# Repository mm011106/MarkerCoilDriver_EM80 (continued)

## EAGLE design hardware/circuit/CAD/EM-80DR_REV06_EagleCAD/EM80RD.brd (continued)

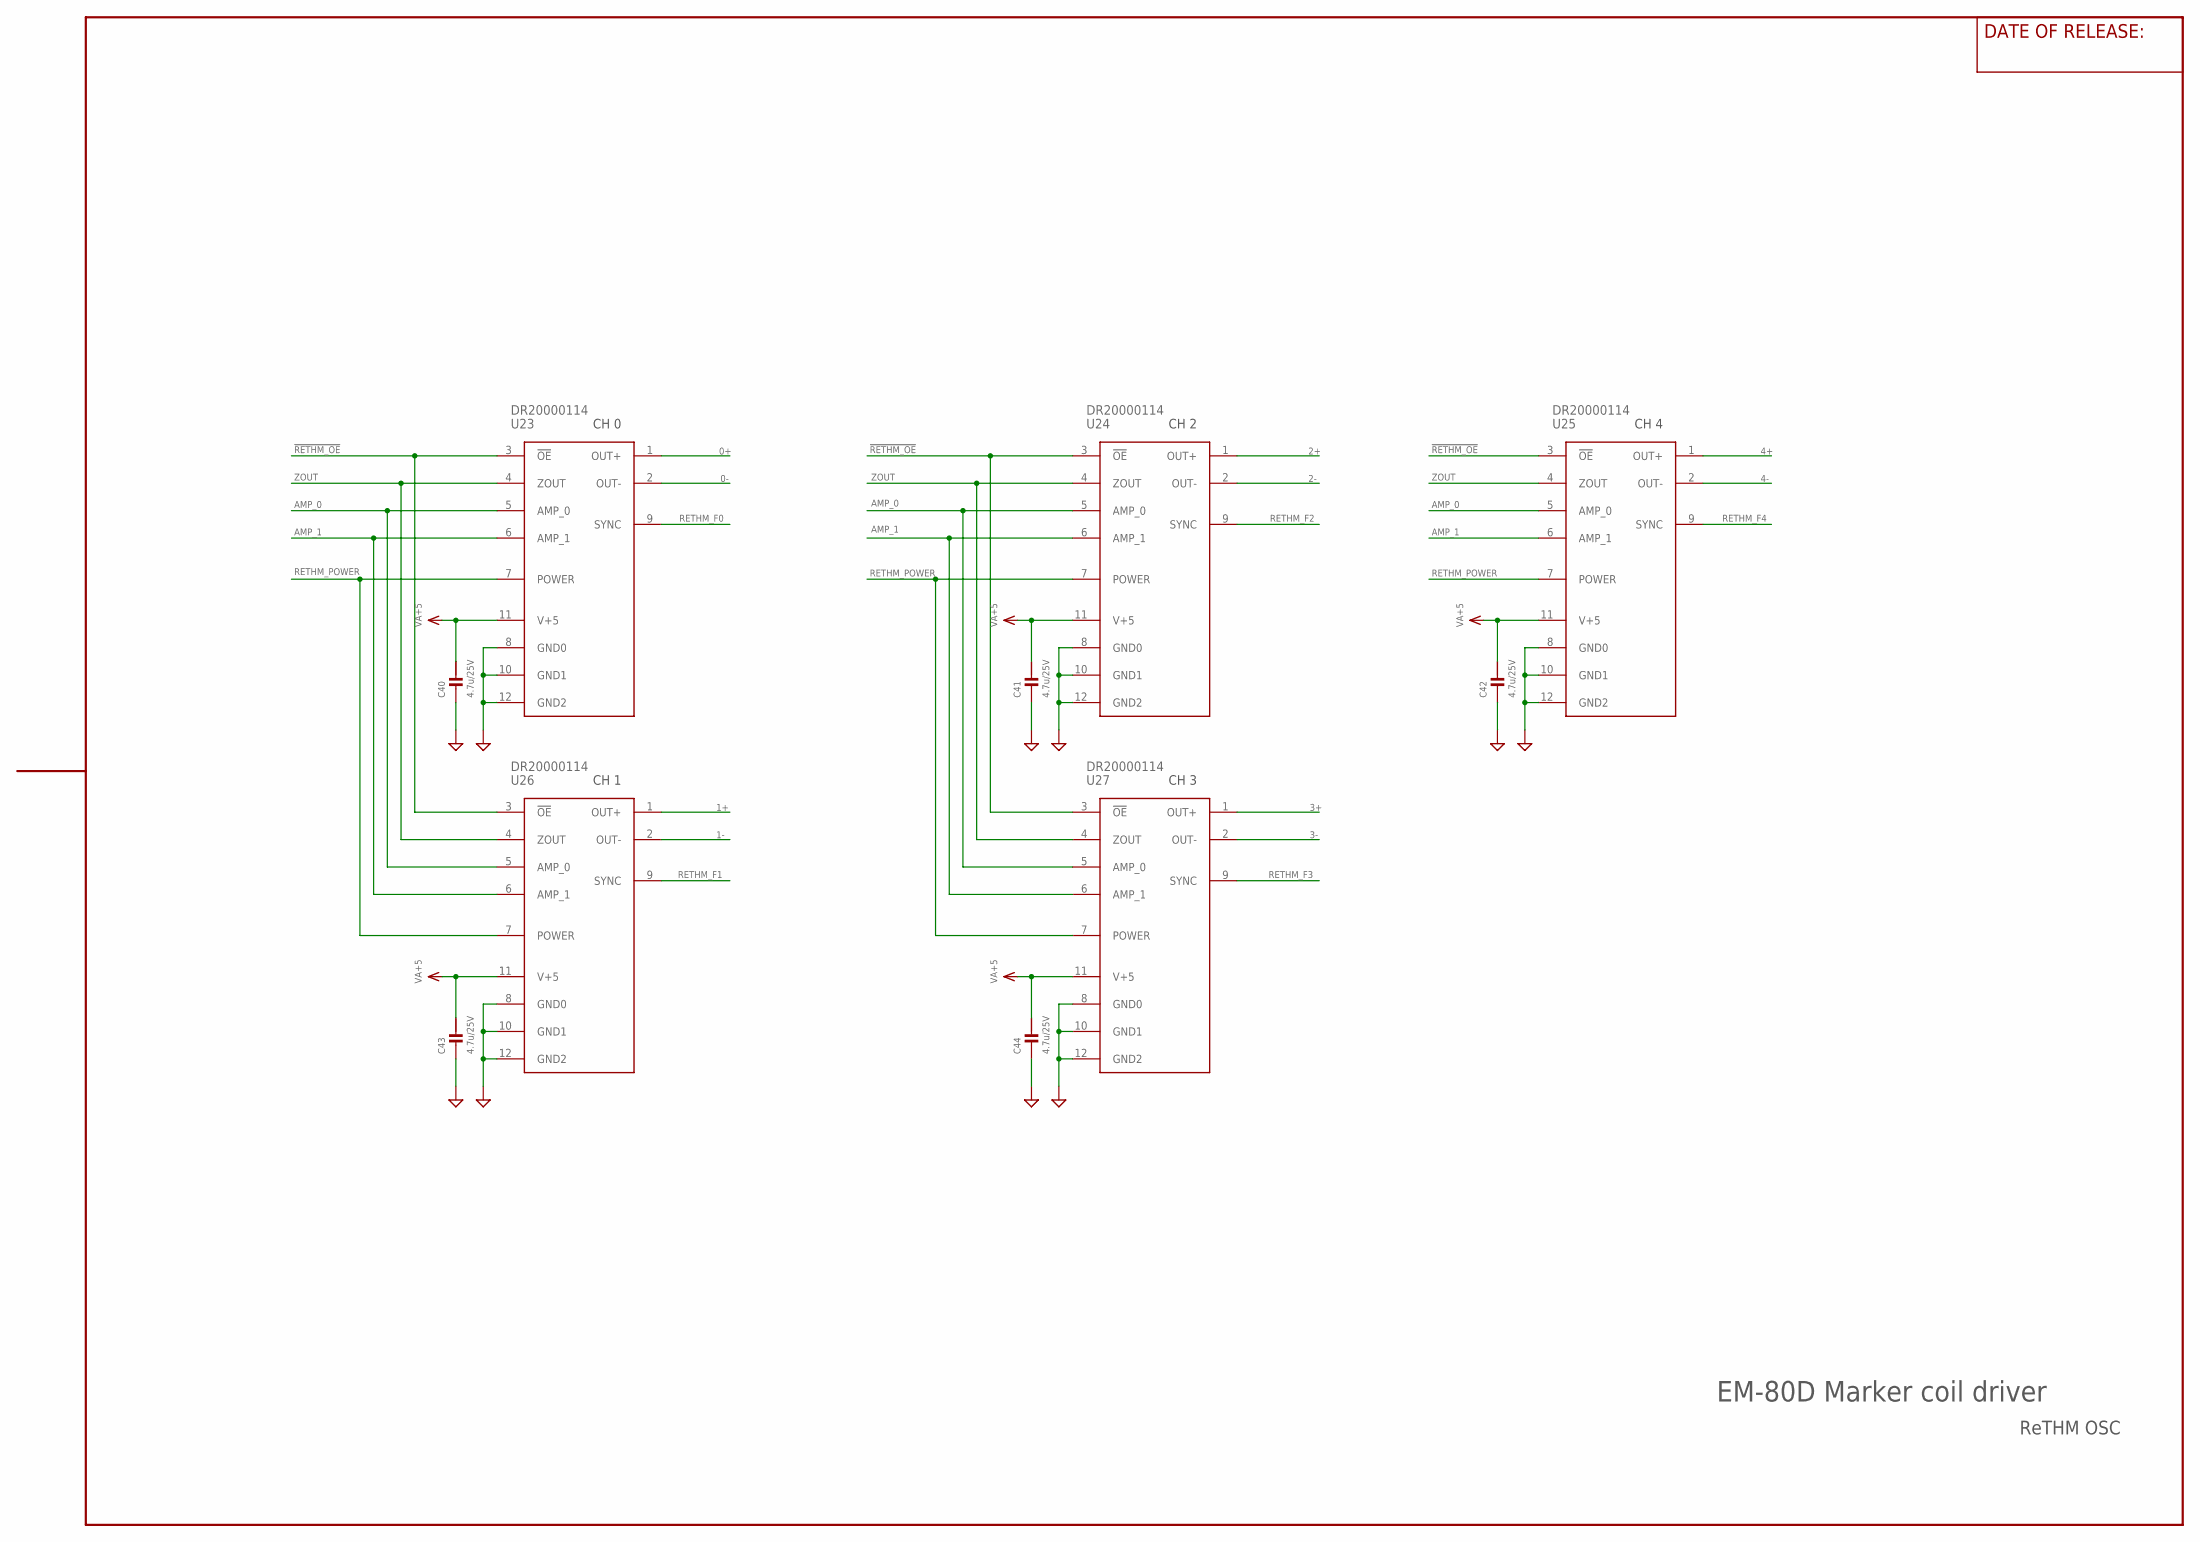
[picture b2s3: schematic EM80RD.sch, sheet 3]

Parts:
C40, C41, C42, C43, C44: 4.7u/25V; CM2012
U23, U24, U25, U26, U27: DR20000114

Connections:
0+: U23.1 (OUT+); also elsewhere on the board
0-: U23.2 (OUT-); also elsewhere on the board
1+: U26.1 (OUT+); also elsewhere on the board
1-: U26.2 (OUT-); also elsewhere on the board
2+: U24.1 (OUT+); also elsewhere on the board
2-: U24.2 (OUT-); also elsewhere on the board
3+: U27.1 (OUT+); also elsewhere on the board
3-: U27.2 (OUT-); also elsewhere on the board
4+: U25.1 (OUT+); also elsewhere on the board
4-: U25.2 (OUT-); also elsewhere on the board
!RETHM_OE: U23.3 (!OE), U24.3 (!OE), U25.3 (!OE), U26.3 (!OE), U27.3 (!OE); also elsewhere on the board
AGND: C40.2, C41.2, C42.2, C43.2, C44.2, U23.8 (GND0), U23.10 (GND1), U23.12 (GND2), U24.8 (GND0), U24.10 (GND1), U24.12 (GND2), U25.8 (GND0), U25.10 (GND1), U25.12 (GND2), U26.8 (GND0), U26.10 (GND1), U26.12 (GND2), U27.8 (GND0), U27.10 (GND1), U27.12 (GND2); also elsewhere on the board
AMP_0: U23.5 (AMP_0), U24.5 (AMP_0), U25.5 (AMP_0), U26.5 (AMP_0), U27.5 (AMP_0); also elsewhere on the board
AMP_1: U23.6 (AMP_1), U24.6 (AMP_1), U25.6 (AMP_1), U26.6 (AMP_1), U27.6 (AMP_1); also elsewhere on the board
RETHM_F0: U23.9 (SYNC); also elsewhere on the board
RETHM_F1: U26.9 (SYNC); also elsewhere on the board
RETHM_F2: U24.9 (SYNC); also elsewhere on the board
RETHM_F3: U27.9 (SYNC); also elsewhere on the board
RETHM_F4: U25.9 (SYNC); also elsewhere on the board
RETHM_POWER: U23.7 (POWER), U24.7 (POWER), U25.7 (POWER), U26.7 (POWER), U27.7 (POWER); also elsewhere on the board
VA+5: C40.1, C41.1, C42.1, C43.1, C44.1, U23.11 (V+5), U24.11 (V+5), U25.11 (V+5), U26.11 (V+5), U27.11 (V+5); also elsewhere on the board
ZOUT: U23.4 (ZOUT), U24.4 (ZOUT), U25.4 (ZOUT), U26.4 (ZOUT), U27.4 (ZOUT); also elsewhere on the board

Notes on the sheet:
ReTHM OSC
CH 0
CH 1
CH 2
CH 3
CH 4
EM-80D Marker coil driver

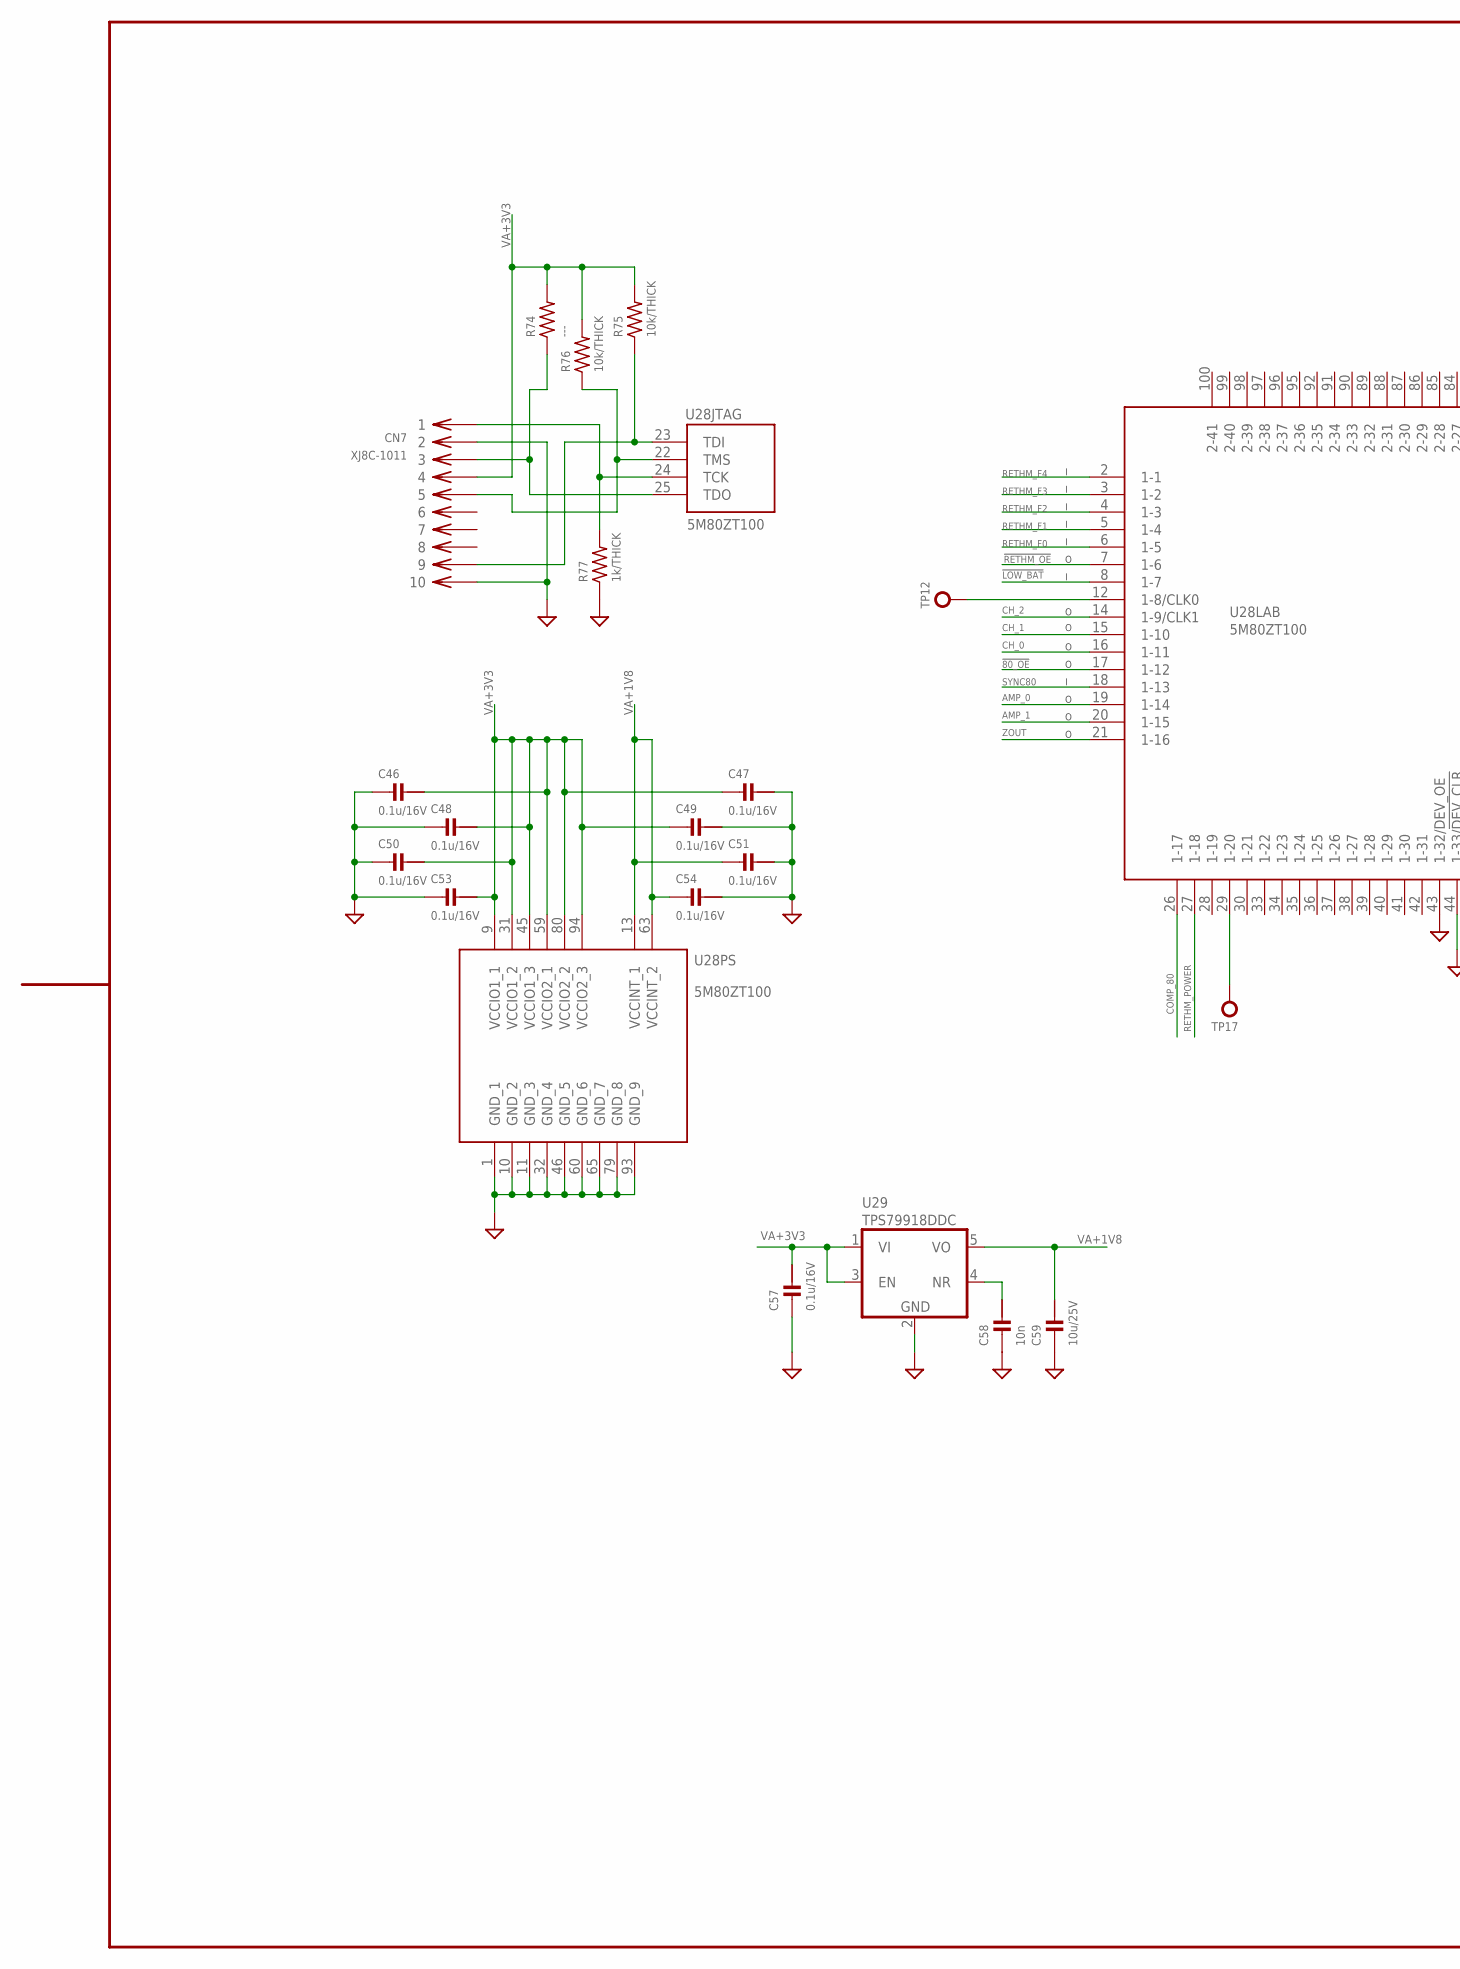
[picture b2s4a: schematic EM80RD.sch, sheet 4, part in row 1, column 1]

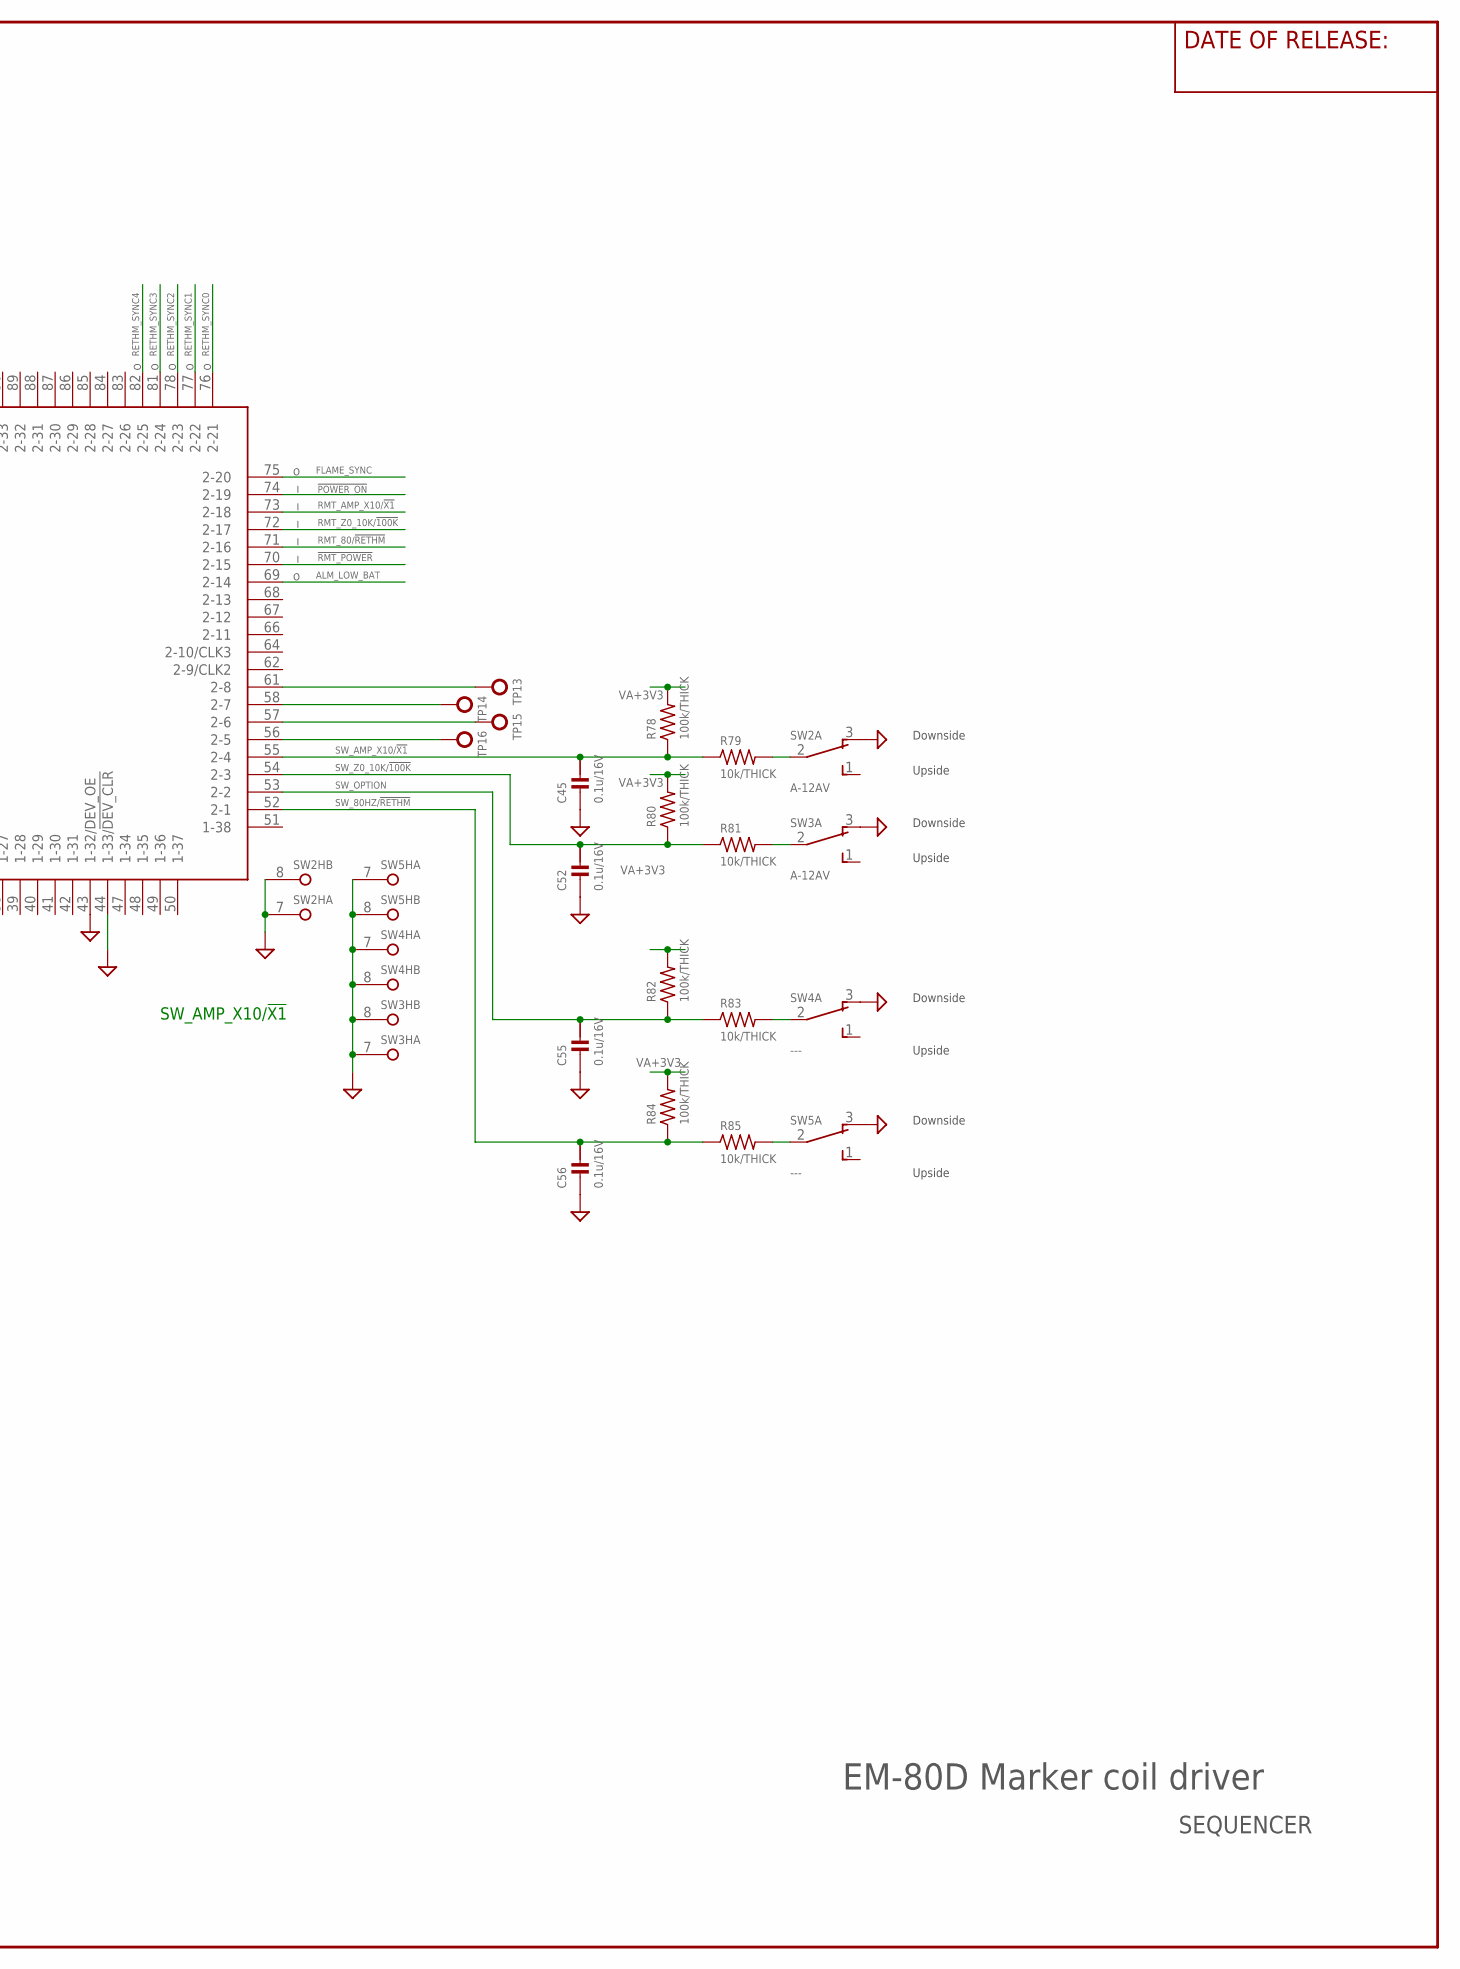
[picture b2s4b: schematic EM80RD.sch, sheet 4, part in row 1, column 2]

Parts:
C45, C46, C47, C48, C49, C50, C51, C52, C53, C54, C55, C56, C57: 0.1u/16V; CM1608
C58: 10n; CM2012
C59: 10u/25V; CM3216
CN7: XJ8C-1011; PIN_HEADER_10PIN
R74: ---; RM1608
R75, R76, R79, R81, R83, R85: 10k/THICK; RM1608
R77: 1k/THICK; RM1608
R78, R80, R82, R84: 100k/THICK; RM1608
SW2, SW3: A-12AV; A-12*
SW4, SW5: ---; A-12*
TP12, TP13, TP14, TP15, TP16, TP17: TP-1PAD; TP_PAD_1MM
U28: 5M80ZT100; QFP100_0.5
U29: TPS79918DDC; SOT-23-5

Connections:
!80_OE: U28.17 (1-12); also elsewhere on the board
!LOW_BAT: U28.8 (1-7); also elsewhere on the board
!POWER_ON: U28.74 (2-19); also elsewhere on the board
!RETHM_OE: U28.7 (1-6); also elsewhere on the board
!RMT_POWER: U28.70 (2-15)
AGND: C45.2, C46.2, C47.1, C48.2, C49.1, C50.2, C51.1, C52.2, C53.2, C54.1, C55.2, C56.2, C57.2, C58.2, C59.2, CN7.2, CN7.10, R77.1, SW2.3 (NC), SW2.7 (BRACKET), SW2.8 (BRACKET), SW3.3 (NC), SW3.7 (BRACKET), SW3.8 (BRACKET), SW4.3 (NC), SW4.7 (BRACKET), SW4.8 (BRACKET), SW5.3 (NC), SW5.7 (BRACKET), SW5.8 (BRACKET), U28.1 (GND_1), U28.10 (GND_2), U28.11 (GND_3), U28.32 (GND_4), U28.43 (1-32/DEV_OE), U28.44 (1-33/!DEV_CLR), U28.46 (GND_5), U28.60 (GND_6), U28.65 (GND_7), U28.79 (GND_8), U28.93 (GND_9), U29.2 (GND); also elsewhere on the board
ALM_LOW_BAT: U28.69 (2-14); also elsewhere on the board
AMP_0: U28.19 (1-14); also elsewhere on the board
AMP_1: U28.20 (1-15); also elsewhere on the board
CH_0: U28.16 (1-11); also elsewhere on the board
CH_1: U28.15 (1-10); also elsewhere on the board
CH_2: U28.14 (1-9/CLK1); also elsewhere on the board
COMP_80: U28.26 (1-17); also elsewhere on the board
FLAME_SYNC: U28.75 (2-20); also elsewhere on the board
unnamed: CN7.9, R75.1, U28.23 (TDI)
unnamed: TP12.P$1, U28.12 (1-8/CLK0)
unnamed: CN7.1, R77.2, U28.24 (TCK)
unnamed: CN7.3, R74.1, U28.25 (TDO)
unnamed: CN7.5, R76.1, U28.22 (TMS)
unnamed: C58.1, U29.4 (NR)
unnamed: TP16.P$1, U28.56 (2-5)
unnamed: TP15.P$1, U28.57 (2-6)
unnamed: TP14.P$1, U28.58 (2-7)
unnamed: TP13.P$1, U28.61 (2-8)
unnamed: TP17.P$1, U28.29 (1-20)
unnamed: R85.2, SW5.2 (C)
unnamed: R83.2, SW4.2 (C)
unnamed: R81.2, SW3.2 (C)
unnamed: R79.2, SW2.2 (C)
RETHM_F0: U28.6 (1-5); also elsewhere on the board
RETHM_F1: U28.5 (1-4); also elsewhere on the board
RETHM_F2: U28.4 (1-3); also elsewhere on the board
RETHM_F3: U28.3 (1-2); also elsewhere on the board
RETHM_F4: U28.2 (1-1); also elsewhere on the board
RETHM_POWER: U28.27 (1-18); also elsewhere on the board
RETHM_SYNC0: U28.76 (2-21)
RETHM_SYNC1: U28.77 (2-22)
RETHM_SYNC2: U28.78 (2-23)
RETHM_SYNC3: U28.81 (2-24)
RETHM_SYNC4: U28.82 (2-25)
RMT_80/!RETHM: U28.71 (2-16); also elsewhere on the board
RMT_AMP_X10/!X1: U28.73 (2-18)
RMT_Z0_10K/!100K: U28.72 (2-17)
SW_80HZ/!RETHM: C56.1, R84.1, R85.1, U28.52 (2-1)
SW_AMP_X10/!X1: C45.1, R78.1, R79.1, U28.55 (2-4)
SW_OPTION: C55.1, R82.1, R83.1, U28.53 (2-2)
SW_Z0_10K/!100K: C52.1, R80.1, R81.1, U28.54 (2-3)
SYNC80: U28.18 (1-13); also elsewhere on the board
VA+1V8: C51.2, C54.2, C59.1, U28.13 (VCCINT_1), U28.63 (VCCINT_2), U29.5 (VO)
VA+3V3: C46.1, C47.2, C48.1, C49.2, C50.1, C53.1, C57.1, CN7.4, R74.2, R75.2, R76.2, R78.2, R80.2, R82.2, R84.2, U28.9 (VCCIO1_1), U28.31 (VCCIO1_2), U28.45 (VCCIO1_3), U28.59 (VCCIO2_1), U28.80 (VCCIO2_2), U28.94 (VCCIO2_3), U29.1 (VI), U29.3 (EN); also elsewhere on the board
ZOUT: U28.21 (1-16); also elsewhere on the board

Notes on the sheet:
Upside
Downside
SEQUENCER
EM-80D Marker coil driver
SW_AMP_X10/!X1

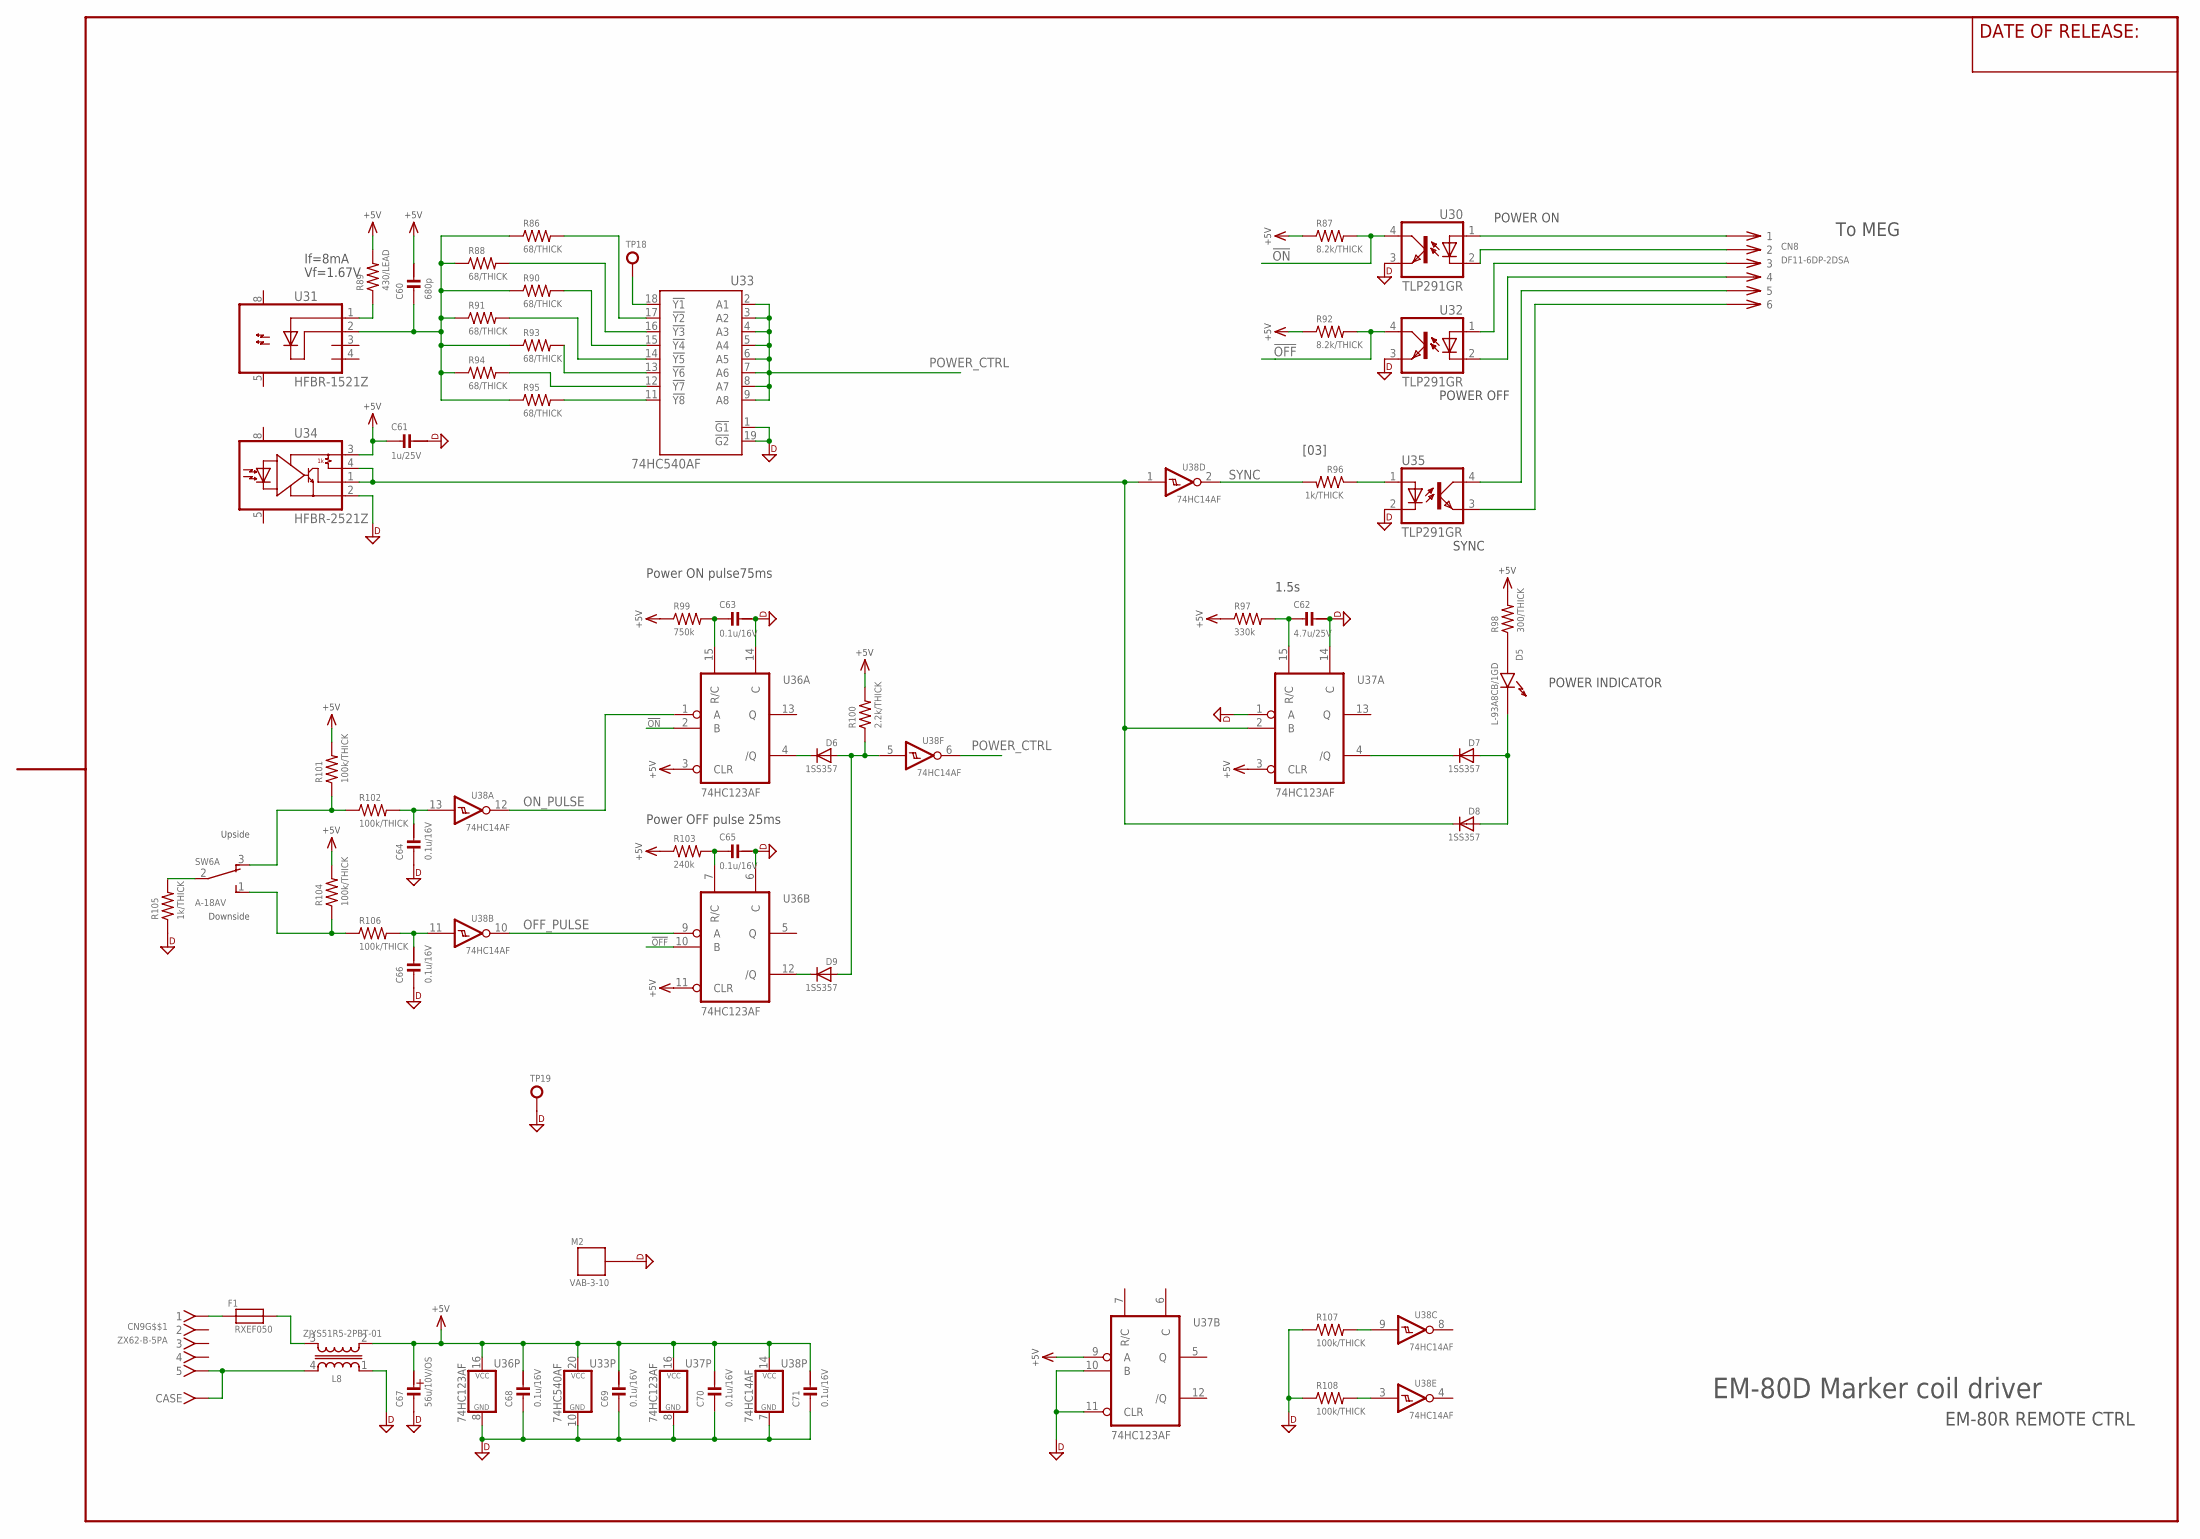
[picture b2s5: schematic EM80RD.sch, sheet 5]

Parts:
C60: 680p; CM1608
C61: 1u/25V; CM2012
C62: 4.7u/25V; CM2012
C63, C65: 0.1u/16V; CM2012
C64, C66, C68, C69, C70, C71: 0.1u/16V; CM1608
C67: 56u/10V/OS; PHI_6.3
CN8: DF11-6DP-2DSA
CN9: ZX62-B-5PA
D5: L-93A8CB/1GD; L-93A8CB
D6, D7, D8, D9: 1SS357; SOD323-R
F1: RXEF050; 8X3/5.08
L8: ZJYS51R5-2PBT-01; ZJYS51-2
M2: VAB-3-10; VAB_3_10_CONTACT
R86, R88, R90, R91, R93, R94, R95: 68/THICK; RM1608
R87, R92: 8.2k/THICK; RM1608
R89: 430/LEAD; 0207/2V
R96, R105: 1k/THICK; RM1608
R97: 330k; RM1608
R98: 300/THICK; RM1608
R99: 750k; RM1608
R100: 2.2k/THICK; RM1608
R101, R102, R104, R106, R107, R108: 100k/THICK; RM1608
R103: 240k; RM1608
SW6: A-18AV; A-12*
TP18, TP19: TP-LC3G; TP_TH_0R9MM
U30, U32, U35: TLP291GR; SO4(11-3C1)(TOSHIBA)
U31: HFBR-1521Z; HFBR-X52X
U33: 74HC540AF; SO20_300MIL
U34: HFBR-2521Z; HFBR-X52X
U36, U37: 74HC123AF; SO16_300MIL
U38: 74HC14AF; SO14_300MIL

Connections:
!OFF: R92.2, U32.4 (COL), U36.10 (B)
!ON: R87.2, U30.4 (COL), U36.2 (B)
DGND: C61.1, C62.1, C63.1, C64.2, C65.1, C66.2, C67.NEG, C68.2, C69.2, C70.2, C71.2, L8.1 (2), M2.CASE1, R105.1, R107.1, R108.1, TP19.1, U30.3 (EMI), U32.3 (EMI), U33.1 (!G1), U33.10 (GND), U33.19 (!G2), U34.2 (GND), U35.2 (C), U36.6 (C), U36.8 (GND), U36.14 (C), U37.1 (A), U37.8 (GND), U37.10 (B), U37.11 (CLR), U37.14 (C), U38.7 (GND); also elsewhere on the board
unnamed: C64.1, R102.2, U38.13 (I)
unnamed: R86.2, U33.17 (!Y2)
unnamed: R90.2, U33.15 (!Y4)
unnamed: R91.2, U33.14 (!Y5)
unnamed: R93.2, U33.13 (!Y6)
unnamed: R94.2, U33.12 (!Y7)
unnamed: R88.2, U33.16 (!Y3)
unnamed: TP18.1, U33.18 (!Y1)
unnamed: C60.2, R86.1, R88.1, R90.1, R91.1, R93.1, R94.1, R95.1, U31.2 (C)
unnamed: C66.1, R106.2, U38.11 (I)
unnamed: R104.1, R106.1, SW6.1 (NO)
unnamed: R101.1, R102.1, SW6.3 (NC)
unnamed: R105.2, SW6.2 (C)
unnamed: D7.C, U37.4 (/Q)
unnamed: R89.1, U31.1 (A)
unnamed: D8.C, U34.1 (VO), U34.4 (RL), U37.2 (B), U38.1 (I)
unnamed: CN9.1, F1.1
unnamed: CN9.5, CN9.C1 (CASE1), CN9.C2 (CASE2), CN9.C3 (CASE3), CN9.C4 (CASE4), CN9.C5 (CASE5), CN9.C6 (CASE), L8.4 (1)
unnamed: F1.2, L8.3
unnamed: C62.2, R97.2, U37.15 (R/C)
unnamed: CN8.1, U30.1 (A)
unnamed: R96.1, U35.1 (A)
unnamed: CN8.2, U30.2 (C)
unnamed: CN8.3, U32.1 (A)
unnamed: CN8.4, U32.2 (C)
unnamed: CN8.5, U35.4 (COL)
unnamed: CN8.6, U35.3 (EMI)
unnamed: D5.A (A1), R98.1
unnamed: D5.C (K1), D7.A, D8.A
unnamed: C65.2, R103.2, U36.7 (R/C)
unnamed: D6.C, U36.4 (/Q)
unnamed: D9.C, U36.12 (/Q)
unnamed: D6.A, D9.A, R100.1, U38.5 (I)
unnamed: C63.2, R99.2, U36.15 (R/C)
unnamed: R95.2, U33.11 (!Y8)
unnamed: R107.2, U38.9 (I)
unnamed: R108.2, U38.3 (I)
OFF_PULSE: U36.9 (A), U38.10 (O)
ON_PULSE: U36.1 (A), U38.12 (O)
POWER_CTRL: U33.2 (A1), U33.3 (A2), U33.4 (A3), U33.5 (A4), U33.6 (A5), U33.7 (A6), U33.8 (A7), U33.9 (A8), U38.6 (O)
SYNC: R96.2, U38.2 (O)
V+5: C60.1, C61.2, C67.POS, C68.1, C69.1, C70.1, C71.1, L8.2 (4), R87.1, R89.2, R92.1, R97.1, R98.2, R99.1, R100.2, R101.2, R103.1, R104.2, U33.20 (VCC), U34.3 (VCC), U36.3 (CLR), U36.11 (CLR), U36.16 (VCC), U37.3 (CLR), U37.9 (A), U37.16 (VCC), U38.14 (VCC)

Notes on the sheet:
If=8mA
Vf=1.67V
EM-80R REMOTE CTRL
Power ON pulse75ms
POWER ON
POWER OFF
SYNC
Upside
Downside
Power OFF pulse 25ms
POWER INDICATOR
1.5s
EM-80D Marker coil driver
To MEG
[03]

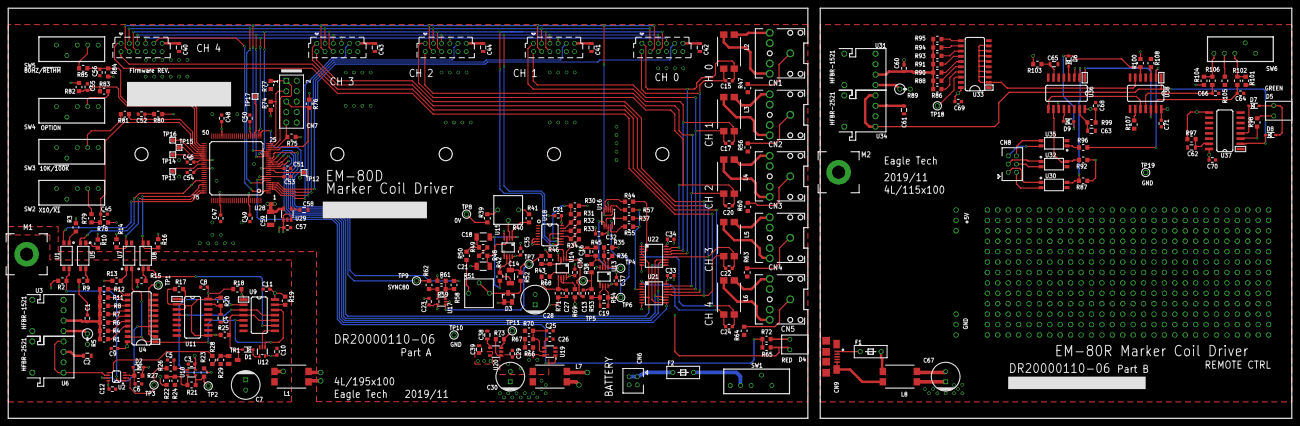
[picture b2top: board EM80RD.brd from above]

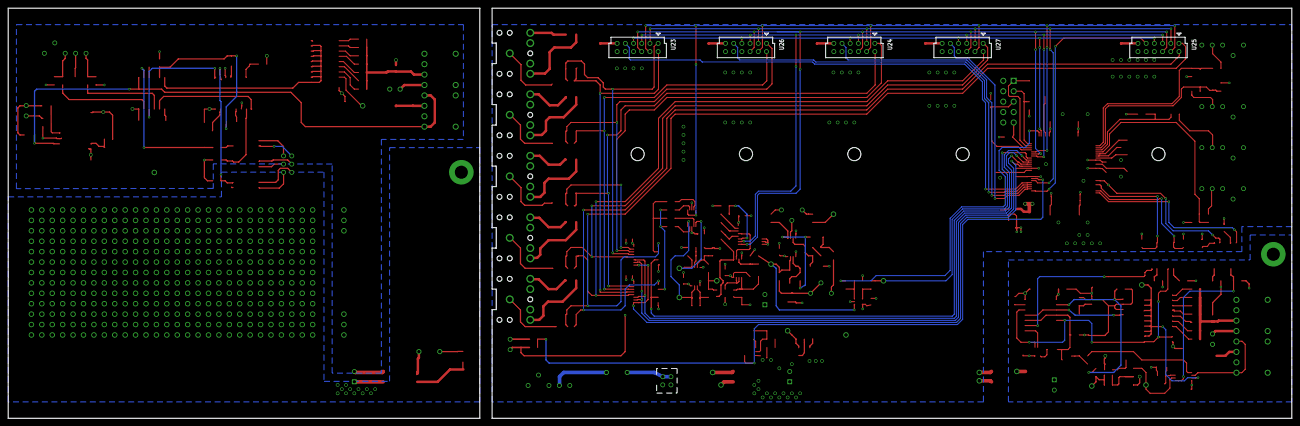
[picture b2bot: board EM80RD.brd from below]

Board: 4 copper layers, 313.0 x 100.0 mm, 273 parts (5 on the bottom side), 194 nets.

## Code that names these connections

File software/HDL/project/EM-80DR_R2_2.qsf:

# -------------------------------------------------------------------------- #
#
# Copyright (C) 1991-2013 Altera Corporation
# Your use of Altera Corporation's design tools, logic functions
# and other software and tools, and its AMPP partner logic
# functions, and any output files from any of the foregoing
# (including device programming or simulation files), and any
# associated documentation or information are expressly subject
# to the terms and conditions of the Altera Program License
# Subscription Agreement, Altera MegaCore Function License
# Agreement, or other applicable license agreement, including,
# without limitation, that your use is for the sole purpose of
# programming logic devices manufactured by Altera and sold by
# Altera or its authorized distributors.  Please refer to the
# applicable agreement for further details.
#
# -------------------------------------------------------------------------- #
#
# Quartus II 32-bit
# Version 13.0.1 Build 232 06/12/2013 Service Pack 1 SJ Web Edition
# Date created = 12:04:04  June 24, 2014
#
# -------------------------------------------------------------------------- #
#
# Notes:
#
# 1) The default values for assignments are stored in the file:
#		EM-80DR_R2_2_assignment_defaults.qdf
#    If this file doesn't exist, see file:
#		assignment_defaults.qdf
#
# 2) Altera recommends that you do not modify this file. This
#    file is updated automatically by the Quartus II software
#    and any changes you make may be lost or overwritten.
#
# -------------------------------------------------------------------------- #


set_global_assignment -name FAMILY "MAX V"
set_global_assignment -name DEVICE 5M80ZT100C5
set_global_assignment -name TOP_LEVEL_ENTITY top
set_global_assignment -name ORIGINAL_QUARTUS_VERSION "13.0 SP1"
set_global_assignment -name PROJECT_CREATION_TIME_DATE "13:13:10  APRIL 18, 2022"
set_global_assignment -name LAST_QUARTUS_VERSION "13.0 SP1"
set_global_assignment -name PROJECT_OUTPUT_DIRECTORY output_files
set_global_assignment -name MIN_CORE_JUNCTION_TEMP 0
set_global_assignment -name MAX_CORE_JUNCTION_TEMP 85
set_global_assignment -name DEVICE_FILTER_PACKAGE TQFP
set_global_assignment -name DEVICE_FILTER_PIN_COUNT 100
set_global_assignment -name DEVICE_FILTER_SPEED_GRADE 5
set_global_assignment -name ERROR_CHECK_FREQUENCY_DIVISOR "-1"
set_global_assignment -name EDA_SIMULATION_TOOL "ModelSim-Altera (VHDL)"
set_global_assignment -name EDA_OUTPUT_DATA_FORMAT VHDL -section_id eda_simulation
set_global_assignment -name VHDL_FILE TOP_MKcoilDriver.vhd
set_global_assignment -name STRATIX_DEVICE_IO_STANDARD "3.3-V LVTTL"
set_instance_assignment -name CURRENT_STRENGTH_NEW 8MA -to AMP[1]
set_instance_assignment -name CURRENT_STRENGTH_NEW 8MA -to AMP[0]
set_instance_assignment -name CURRENT_STRENGTH_NEW 8MA -to CH[2]
set_instance_assignment -name CURRENT_STRENGTH_NEW 8MA -to CH[1]
set_instance_assignment -name CURRENT_STRENGTH_NEW 8MA -to CH[0]
set_instance_assignment -name IO_STANDARD "3.3V SCHMITT TRIGGER INPUT" -to SW_ZO_10k_100k
set_instance_assignment -name IO_STANDARD "3.3V SCHMITT TRIGGER INPUT" -to SW_AMP_x10_x1
set_instance_assignment -name CURRENT_STRENGTH_NEW 8MA -to ZOUT
set_instance_assignment -name IO_STANDARD "3.3V SCHMITT TRIGGER INPUT" -to SW_80_nRETHM
set_instance_assignment -name IO_STANDARD "3.3V SCHMITT TRIGGER INPUT" -to SW_OPTION
set_instance_assignment -name CURRENT_STRENGTH_NEW 8MA -to nRETHM_OE
set_instance_assignment -name CURRENT_STRENGTH_NEW 8MA -to n80_OE
set_instance_assignment -name CURRENT_STRENGTH_NEW 8MA -to CMP_80
set_instance_assignment -name IO_STANDARD "3.3V SCHMITT TRIGGER INPUT" -to RMT_80_nRETHM
set_instance_assignment -name CURRENT_STRENGTH_NEW 8MA -to ALM_LOW_BAT
set_instance_assignment -name CURRENT_STRENGTH_NEW 8MA -to RETHM_POWER
set_instance_assignment -name IO_STANDARD "3.3V SCHMITT TRIGGER INPUT" -to nPOWER_ON
set_global_assignment -name OPTIMIZE_HOLD_TIMING "IO PATHS AND MINIMUM TPD PATHS"
set_global_assignment -name OPTIMIZE_MULTI_CORNER_TIMING OFF
set_global_assignment -name OPTIMIZE_POWER_DURING_FITTING "EXTRA EFFORT"
set_instance_assignment -name CURRENT_STRENGTH_NEW 8MA -to nSYNC
set_location_assignment PIN_69 -to ALM_LOW_BAT
set_location_assignment PIN_20 -to AMP[1]
set_location_assignment PIN_19 -to AMP[0]
set_location_assignment PIN_14 -to CH[2]
set_location_assignment PIN_15 -to CH[1]
set_location_assignment PIN_16 -to CH[0]
set_location_assignment PIN_18 -to CLK
set_location_assignment PIN_26 -to CMP_80
set_location_assignment PIN_17 -to n80_OE
set_location_assignment PIN_8 -to nLOW_BATT
set_location_assignment PIN_74 -to nPOWER_ON
set_location_assignment PIN_7 -to nRETHM_OE
set_location_assignment PIN_75 -to nSYNC
set_location_assignment PIN_6 -to RETHM_F0
set_location_assignment PIN_5 -to RETHM_F1
set_location_assignment PIN_4 -to RETHM_F2
set_location_assignment PIN_3 -to RETHM_F3
set_location_assignment PIN_2 -to RETHM_F4
set_location_assignment PIN_27 -to RETHM_POWER
set_location_assignment PIN_71 -to RMT_80_nRETHM
set_location_assignment PIN_52 -to SW_80_nRETHM
set_location_assignment PIN_55 -to SW_AMP_x10_x1
set_location_assignment PIN_53 -to SW_OPTION
set_location_assignment PIN_54 -to SW_ZO_10k_100k
set_location_assignment PIN_21 -to ZOUT

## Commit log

2024-09-25 revise LICENSE.md
2024-09-27 図面ファイル追加
2024-09-27 ファイル追加
2024-10-09 回路図のreadmeを追記
2024-10-09 add files
2024-10-15 Add Readme in CAD
2024-10-15 回路図のdesign_noteを追記
2025-02-10 回路動作解説 追記
2025-02-12 回路のdesgin_note.mdに追記
2025-02-12 回路のdesgin_note.mdを修正
2025-02-19 コメント追記
2025-02-19 コメント追記・ファイル追加
2025-02-19 コメント変更
2025-02-19 HDL設計ノート記入
2025-02-20 タイミングチャート作成
2025-02-20 コメント追加
2025-03-03 add files for HDL compile
2025-03-03 add comment and note
2025-03-03 修正履歴追加
2025-03-05 表現の見直し
2025-03-12 追記・修正
2025-03-12 Remove .vscode folder from repository
2025-03-12 add note to README.md
2025-03-17 .docxをPDFに変換
